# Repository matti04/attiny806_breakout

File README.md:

PLEASE VISIT MY WEBSITE BEFORE USING ANY OF THE PROVIDED FILES!

https://matti04.net/files/attiny/

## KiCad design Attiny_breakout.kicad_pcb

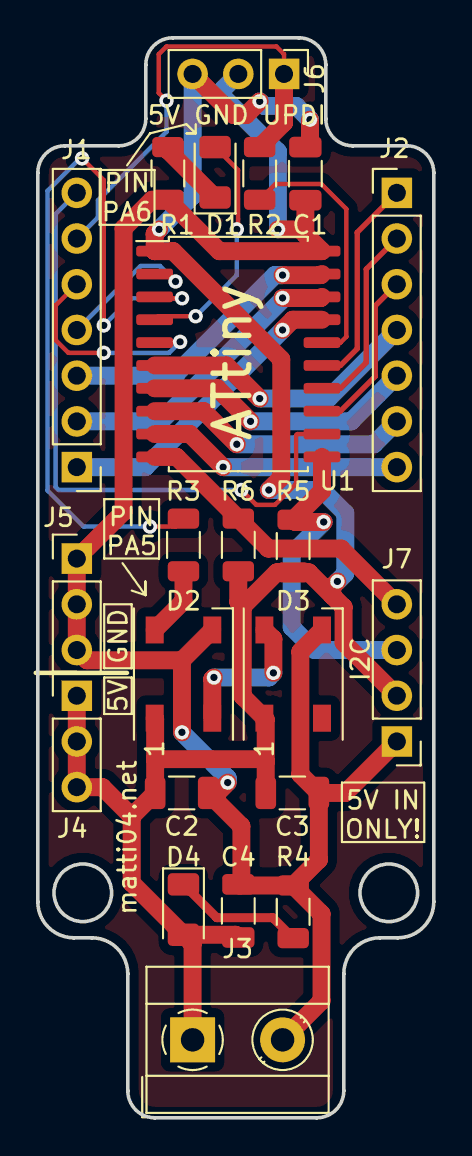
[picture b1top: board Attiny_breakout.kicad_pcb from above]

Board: 2 copper layers, 22.0 x 60.0 mm, 22 parts (0 on the bottom side), 25 nets.

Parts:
C1, C2, C3: 0,1µF; C_1206_3216Metric
C4: 10µF; C_1206_3216Metric
D1, D4: LED; LED_1206_3216Metric
D2, D3: WS2812B; LED_WS2812B_PLCC4_5.0x5.0mm_P3.2mm
J1: Con_PA; PinHeader_1x07_P2.54mm_Vertical
J2: Con_PB; PinHeader_1x07_P2.54mm_Vertical
J3: Screw; TerminalBlock_MetzConnect_Type055_RT01502HDWU_1x02_P5.00mm_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
J4: 5V; PinHeader_1x03_P2.54mm_Vertical
J5: GND; PinHeader_1x03_P2.54mm_Vertical
J6: UPDI_Programmer; PinHeader_1x03_P2.54mm_Vertical
J7: IC2; PinHeader_1x04_P2.54mm_Vertical
R1, R3, R4: 330Ω; R_1206_3216Metric
R2: 470Ω; R_1206_3216Metric
R5, R6: 10kΩ; R_1206_3216Metric
U1: ATtiny806; SOIC-20W_7.5x12.8mm_P1.27mm

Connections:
+5V: C1.1, C2.2, C3.2, C4.1, D2.1, D3.1, D4.2, J3.1, J4.1, J4.2, J4.3, J6.3, J7.2, R5.1, R6.1, U1.1
/NeoPixel: R3.2, U1.3
/PA1: J1.1, U1.17
/PA2: J1.2, U1.18
/PA3: J1.3, U1.19
/PA4: J1.4, U1.2
/PA7: J1.5, U1.5
/PB2: J2.7, U1.9
/PB3: J2.6, U1.8
/PB4: J2.5, U1.7
/PB5: J2.4, U1.6
/PC0: J1.7, U1.12
/PC1: J2.3, U1.13
/PC2: J2.2, U1.14
/PC3: J2.1, U1.15
/SCL: J7.3, R5.2, U1.11
/SDA: J7.4, R6.2, U1.10
/UPDI: J1.6, J6.1, R2.1
GND: C1.2, C2.1, C3.1, C4.2, D2.3, D3.3, J3.2, J5.1, J5.2, J5.3, J6.2, J7.1, R1.2, R4.2, U1.20
unnamed: D1.1, R1.1
unnamed: D1.2, U1.4
unnamed: D2.2, D3.4
unnamed: D2.4, R3.1
unnamed: D4.1, R4.1
unnamed: R2.2, U1.16
